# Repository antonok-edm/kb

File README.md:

# kb
This repository contains the full design files for my custom-designed keyboard.

Features:
- 68 keys
- compact ortholinear format
- carbon fiber construction
- full on-the-fly programmability
- HID Mouse functionality
- MIDI functionality
- Built-in Colemak layout
- 14-key HID rollover
- n-key MIDI rollover
- multiple function layers

## My setup
The keyboard's layouts are designed to be reprogrammed as needed. The user is free to assign keys to any HID-compliant controls or internal function calls at will. In this section, I describe the layouts that I use, included as a sample in this repository.

I currently have 7 different layers defined on my keyboard: Colemak, Qwerty, MIDI, Fn, Layer-Up, Layer-Down, and Mouse.

MIDI has a 4x12 grid of chromatic MIDI keys, providing 4 octaves of pitch-shiftable notes.

Fn has all standard function keys, as well as keyboard-internal functions like switching between layers.

Layer-Down puts symbols for programming, such as parenthesis and braces, on the home row so that they can be accessed more easily.

Layer-Up has a numpad.

Mouse puts cursor controls on the right side of the keyboard, with cursor speed controls operated by the left hand.

## Customizing the keyboard
The tool [kb-layout-manager](https://gitlab.com/antonok/kb-layout-manager) was created to make layout customization extremely easy and intuitive.
Manual customization is still possible by modifying the `layermaps.c` file.

`layermaps.c` includes the behavior of every key. Each key can take one of the following functions:

| Function | Description                                                                     | Examples                                                                 |
|----------|---------------------------------------------------------------------------------|--------------------------------------------------------------------------|
| HID      | Any standard keyboard key                                                       | <kbd>a</kbd>, <kbd>1</kbd>, <kbd>;</kbd>                                 |
| MOD      | At least one standard keyboard modifier                                         | <kbd>Left shift</kbd>, <kbd>Right control</kbd>                          |
| MIDI     | Any MIDI pitch                                                                  | C0 to G10                                                                |
| TOGGLE   | Switch to a different layer                                                     | Change to MIDI layer, switch to QWERTY layout                            |
| TARGET   | Switch to a different layer while the key is held (modifier-style)              | Access FN keys, use temporary layer shifts                               |
| FUNC     | Any arbitrary predefined function from the firmware                             | shift MIDI pitch, switch function layer                                  |
| CLICK    | Execute a click an HID mouse button                                             | left click, middle click, forward/back                                   |
| MOUSE    | Move the mouse cursor                                                           | horizontal or vertical                                                   |
| SCROLL   | Mouse scroll or pan                                                             | horizontal or vertical                                                   |
| HIDMOD   | Any standard keyboard key combined with at least one standard keyboard modifier | <kbd>ctrl</kbd>+<kbd>shift</kbd>+<kbd>m</kbd>, <kbd>{</kbd>, <kbd>?</kbd>|

Once modifications have been made to a layout, the firmware can be reflashed to the keyboard using the standard Teensy programmer over USB. The Teensy's bootloader
can be accessed without taking apart the keyboard by pressing a predefined key combination. The entire reflashing process takes about 3 seconds in total.

## Want to use this for your own keyboard?
If this project is useful at all for you, I'd love to hear about it!

The firmware is optimized for my own personal setup, but could be tweaked with minimal effort to suit different hardware. Please feel free to submit an issue, and I would
be happy to provide assistance with this.

### License information
Files from the LUFA library are released under the MIT license.
My custom design files are released under version 3 or later of the GPL.
License information for the LUFA library is available at www.lufa-lib.org.

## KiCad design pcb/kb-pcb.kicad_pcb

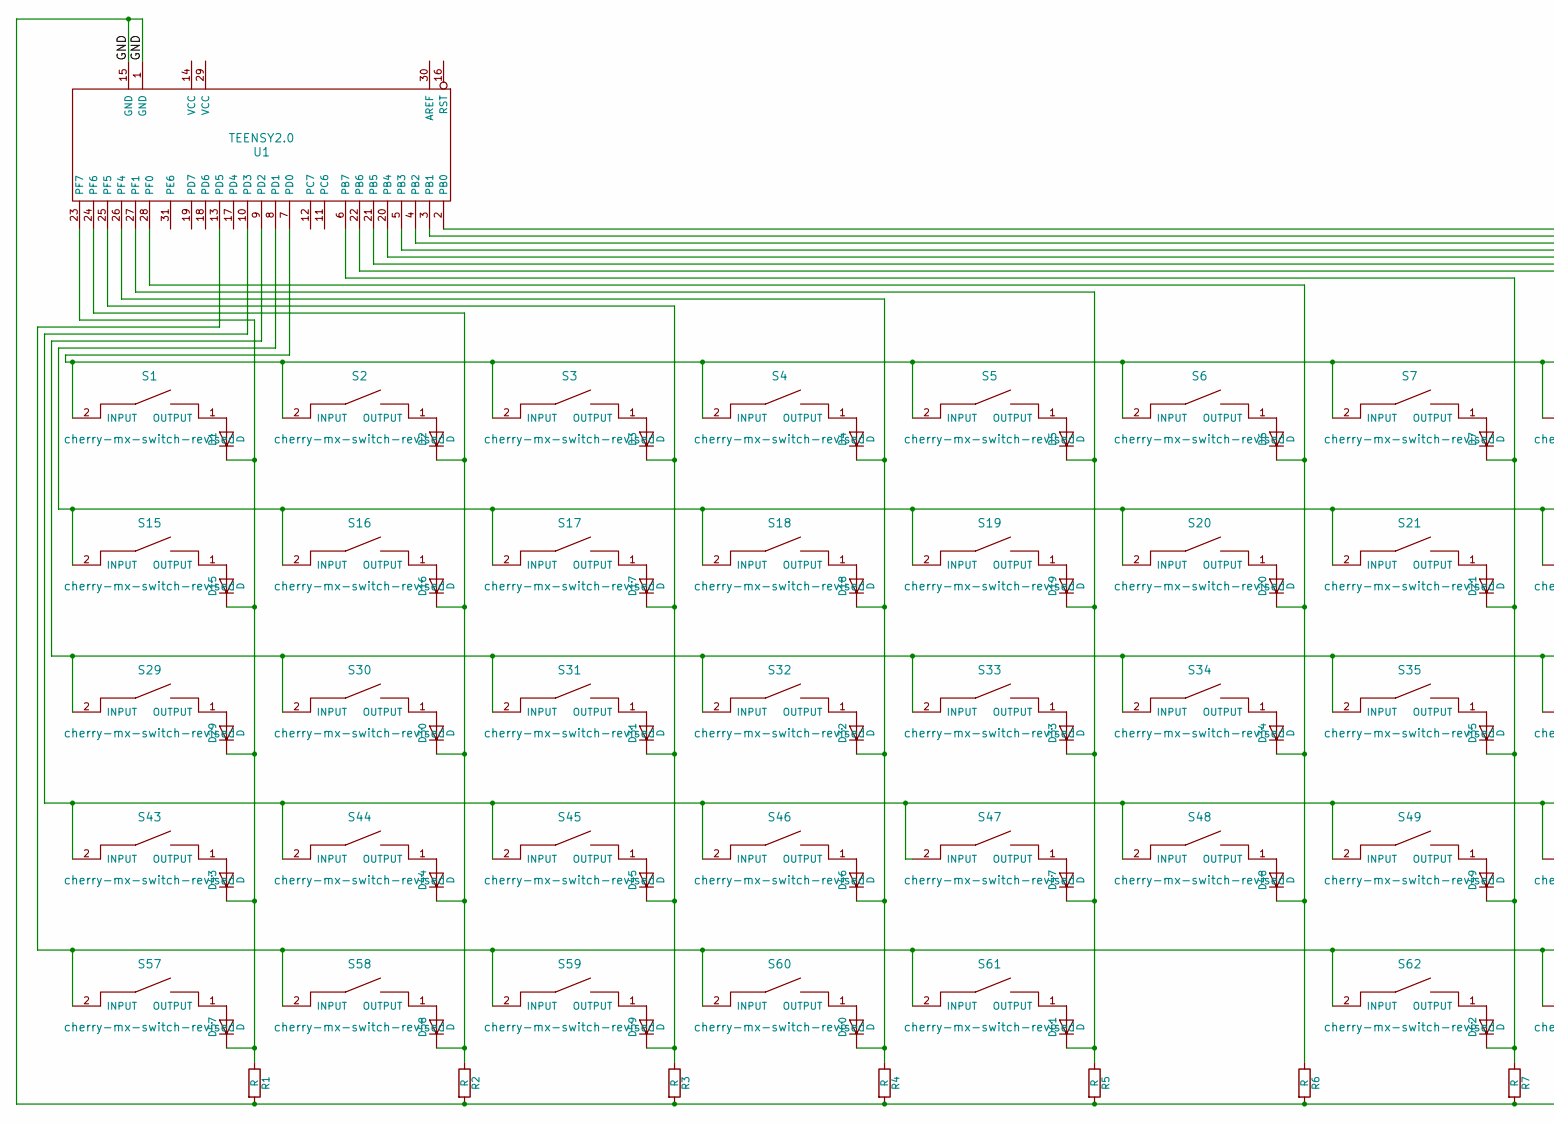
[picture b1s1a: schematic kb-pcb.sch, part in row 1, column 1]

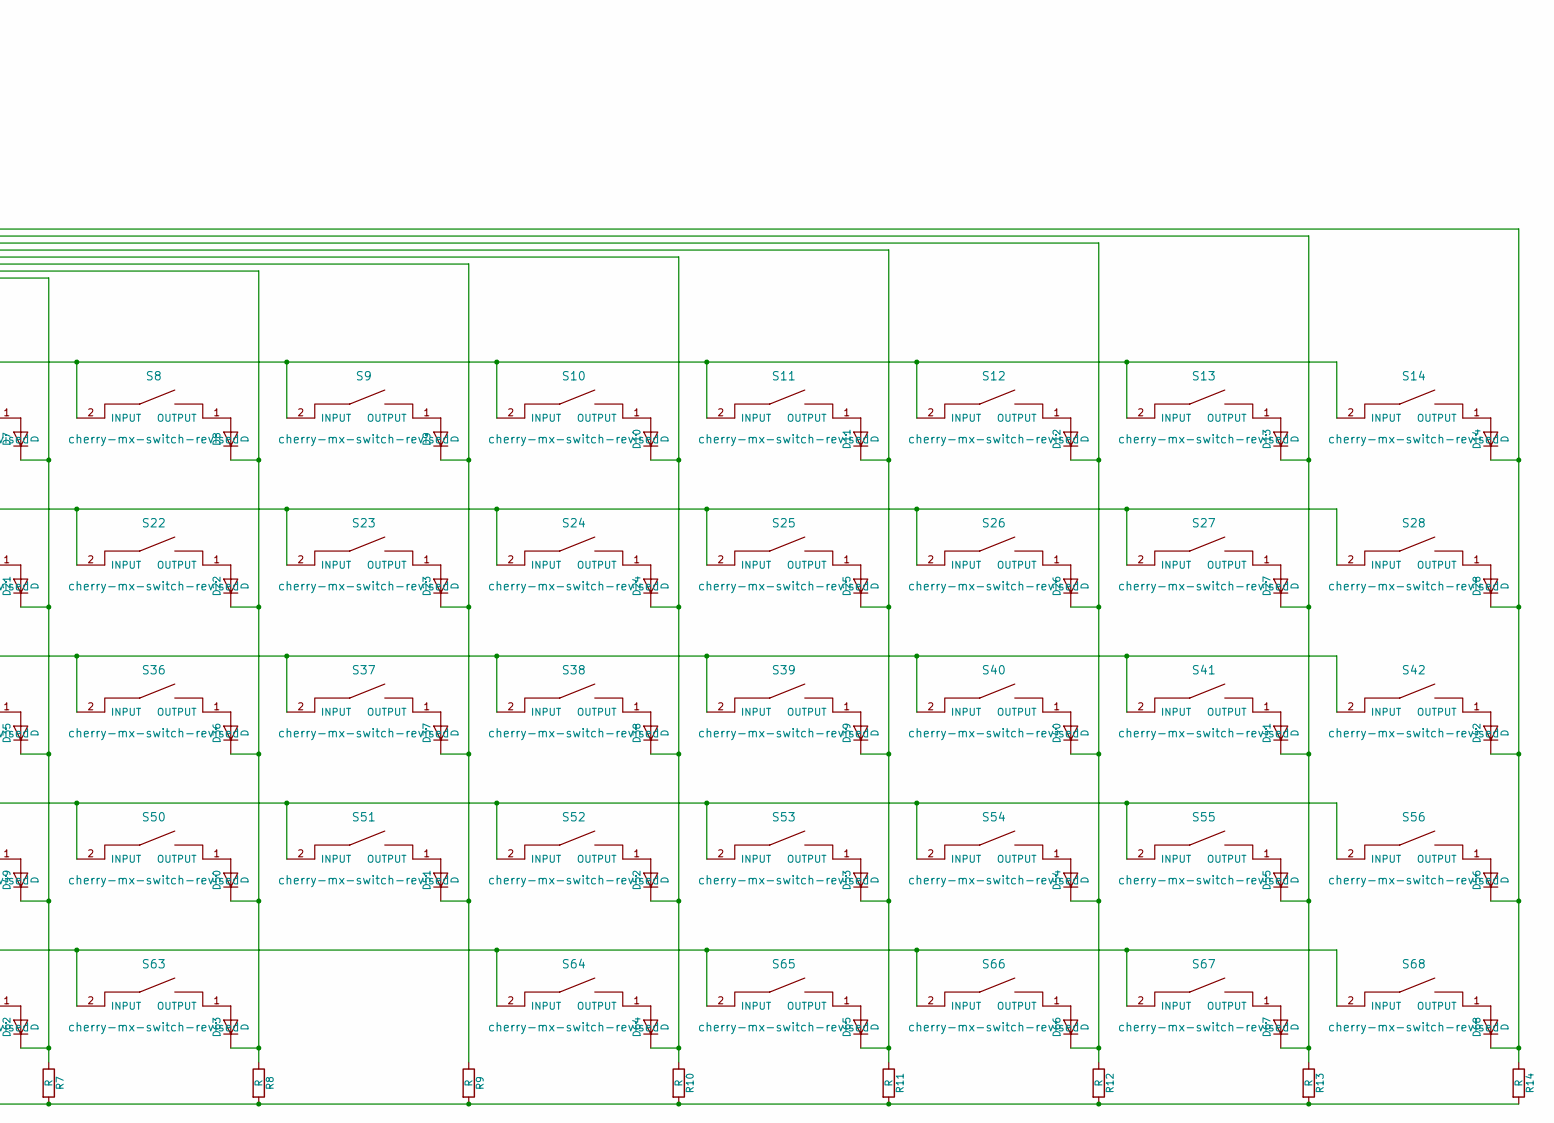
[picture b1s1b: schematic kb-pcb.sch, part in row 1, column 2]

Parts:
D1, D2, D3, D4, D5, D6, D7, D8, D9, D10, D11, D12, D13, D14, D15, D16, D17, D18, D19, D20, D21, D22, D23, D24, D25, D26, D27, D28, D29, D30, D31, D32, D33, D34, D35, D36, D37, D38, D39, D40, D41, D42, D43, D44, D45, D46, D47, D48, D49, D50, D51, D52, D53, D54, D55, D56, D57, D58, D59, D60, D61, D62, D63, D64, D65, D66, D67, D68: D; D_DO-35_SOD27_P7.62mm_Horizontal
R1, R2, R3, R4, R5, R6, R7, R8, R9, R10, R11, R12, R13, R14: R; Resistor_SMD+THTuniversal_0805to2512_RM10_HandSoldering
S1, S2, S3, S4, S5, S6, S7, S8, S9, S10, S11, S12, S13, S14, S15, S16, S17, S18, S19, S20, S21, S22, S23, S24, S25, S26, S27, S28, S29, S30, S31, S32, S33, S34, S35, S36, S37, S38, S39, S40, S41, S42, S43, S44, S45, S46, S47, S48, S49, S50, S51, S52, S53, S54, S55, S56, S57, S58, S59, S60, S65, S66, S67, S68: cherry-mx-switch-revised; key_1u
S61, S63: cherry-mx-switch-revised; key_1.75u
S62, S64: cherry-mx-switch-revised; key_1.25u
U1: TEENSY2.0; Teensy2.0

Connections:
/GND: R1.2, R2.2, R3.2, R4.2, R5.2, R6.2, R7.2, R8.2, R9.2, R10.2, R11.2, R12.2, R13.2, R14.2, U1.1 (GND), U1.15 (GND)
unnamed: D1.1 (K), D15.1 (K), D29.1 (K), D43.1 (K), D57.1 (K), R1.1, U1.23 (PF7)
unnamed: D1.2 (A), S1.1 (OUTPUT)
unnamed: D2.2 (A), S2.1 (OUTPUT)
unnamed: D3.2 (A), S3.1 (OUTPUT)
unnamed: D4.2 (A), S4.1 (OUTPUT)
unnamed: D5.2 (A), S5.1 (OUTPUT)
unnamed: D6.2 (A), S6.1 (OUTPUT)
unnamed: D7.2 (A), S7.1 (OUTPUT)
unnamed: D8.2 (A), S8.1 (OUTPUT)
unnamed: D9.2 (A), S9.1 (OUTPUT)
unnamed: D10.1 (K), D24.1 (K), D38.1 (K), D52.1 (K), D64.1 (K), R10.1, U1.20 (PB4)
unnamed: D10.2 (A), S10.1 (OUTPUT)
unnamed: D11.1 (K), D25.1 (K), D39.1 (K), D53.1 (K), D65.1 (K), R11.1, U1.5 (PB3)
unnamed: D11.2 (A), S11.1 (OUTPUT)
unnamed: D12.1 (K), D26.1 (K), D40.1 (K), D54.1 (K), D66.1 (K), R12.1, U1.4 (PB2)
unnamed: D12.2 (A), S12.1 (OUTPUT)
unnamed: D13.1 (K), D27.1 (K), D41.1 (K), D55.1 (K), D67.1 (K), R13.1, U1.3 (PB1)
unnamed: D13.2 (A), S13.1 (OUTPUT)
unnamed: D14.1 (K), D28.1 (K), D42.1 (K), D56.1 (K), D68.1 (K), R14.1, U1.2 (PB0)
unnamed: D14.2 (A), S14.1 (OUTPUT)
unnamed: D15.2 (A), S15.1 (OUTPUT)
unnamed: D2.1 (K), D16.1 (K), D30.1 (K), D44.1 (K), D58.1 (K), R2.1, U1.24 (PF6)
unnamed: D16.2 (A), S16.1 (OUTPUT)
unnamed: D3.1 (K), D17.1 (K), D31.1 (K), D45.1 (K), D59.1 (K), R3.1, U1.25 (PF5)
unnamed: D17.2 (A), S17.1 (OUTPUT)
unnamed: D4.1 (K), D18.1 (K), D32.1 (K), D46.1 (K), D60.1 (K), R4.1, U1.26 (PF4)
unnamed: D18.2 (A), S18.1 (OUTPUT)
unnamed: D5.1 (K), D19.1 (K), D33.1 (K), D47.1 (K), D61.1 (K), R5.1, U1.27 (PF1)
unnamed: D19.2 (A), S19.1 (OUTPUT)
unnamed: D6.1 (K), D20.1 (K), D34.1 (K), D48.1 (K), R6.1, U1.28 (PF0)
unnamed: D20.2 (A), S20.1 (OUTPUT)
unnamed: D7.1 (K), D21.1 (K), D35.1 (K), D49.1 (K), D62.1 (K), R7.1, U1.6 (PB7)
unnamed: D21.2 (A), S21.1 (OUTPUT)
unnamed: D8.1 (K), D22.1 (K), D36.1 (K), D50.1 (K), D63.1 (K), R8.1, U1.22 (PB6)
unnamed: D22.2 (A), S22.1 (OUTPUT)
unnamed: D9.1 (K), D23.1 (K), D37.1 (K), D51.1 (K), R9.1, U1.21 (PB5)
unnamed: D23.2 (A), S23.1 (OUTPUT)
unnamed: D24.2 (A), S24.1 (OUTPUT)
unnamed: D25.2 (A), S25.1 (OUTPUT)
unnamed: D26.2 (A), S26.1 (OUTPUT)
unnamed: D27.2 (A), S27.1 (OUTPUT)
unnamed: D28.2 (A), S28.1 (OUTPUT)
unnamed: D29.2 (A), S29.1 (OUTPUT)
unnamed: D30.2 (A), S30.1 (OUTPUT)
unnamed: D31.2 (A), S31.1 (OUTPUT)
unnamed: D32.2 (A), S32.1 (OUTPUT)
unnamed: D33.2 (A), S33.1 (OUTPUT)
unnamed: D34.2 (A), S34.1 (OUTPUT)
unnamed: D35.2 (A), S35.1 (OUTPUT)
unnamed: D36.2 (A), S36.1 (OUTPUT)
unnamed: D37.2 (A), S37.1 (OUTPUT)
unnamed: D38.2 (A), S38.1 (OUTPUT)
unnamed: D39.2 (A), S39.1 (OUTPUT)
unnamed: D40.2 (A), S40.1 (OUTPUT)
unnamed: D41.2 (A), S41.1 (OUTPUT)
unnamed: D42.2 (A), S42.1 (OUTPUT)
unnamed: D43.2 (A), S43.1 (OUTPUT)
unnamed: D44.2 (A), S44.1 (OUTPUT)
unnamed: D45.2 (A), S45.1 (OUTPUT)
unnamed: D46.2 (A), S46.1 (OUTPUT)
unnamed: D47.2 (A), S47.1 (OUTPUT)
unnamed: D48.2 (A), S48.1 (OUTPUT)
unnamed: D49.2 (A), S49.1 (OUTPUT)
unnamed: D50.2 (A), S50.1 (OUTPUT)
unnamed: D51.2 (A), S51.1 (OUTPUT)
unnamed: D52.2 (A), S52.1 (OUTPUT)
unnamed: D53.2 (A), S53.1 (OUTPUT)
unnamed: D54.2 (A), S54.1 (OUTPUT)
unnamed: D55.2 (A), S55.1 (OUTPUT)
unnamed: D56.2 (A), S56.1 (OUTPUT)
unnamed: D57.2 (A), S57.1 (OUTPUT)
unnamed: D58.2 (A), S58.1 (OUTPUT)
unnamed: D59.2 (A), S59.1 (OUTPUT)
unnamed: D60.2 (A), S60.1 (OUTPUT)
unnamed: D61.2 (A), S61.1 (OUTPUT)
unnamed: D62.2 (A), S62.1 (OUTPUT)
unnamed: D63.2 (A), S63.1 (OUTPUT)
unnamed: D64.2 (A), S64.1 (OUTPUT)
unnamed: D65.2 (A), S65.1 (OUTPUT)
unnamed: D66.2 (A), S66.1 (OUTPUT)
unnamed: D67.2 (A), S67.1 (OUTPUT)
unnamed: D68.2 (A), S68.1 (OUTPUT)
unnamed: S1.2 (INPUT), S2.2 (INPUT), S3.2 (INPUT), S4.2 (INPUT), S5.2 (INPUT), S6.2 (INPUT), S7.2 (INPUT), S8.2 (INPUT), S9.2 (INPUT), S10.2 (INPUT), S11.2 (INPUT), S12.2 (INPUT), S13.2 (INPUT), S14.2 (INPUT), U1.7 (PD0)
unnamed: S15.2 (INPUT), S16.2 (INPUT), S17.2 (INPUT), S18.2 (INPUT), S19.2 (INPUT), S20.2 (INPUT), S21.2 (INPUT), S22.2 (INPUT), S23.2 (INPUT), S24.2 (INPUT), S25.2 (INPUT), S26.2 (INPUT), S27.2 (INPUT), S28.2 (INPUT), U1.8 (PD1)
unnamed: S29.2 (INPUT), S30.2 (INPUT), S31.2 (INPUT), S32.2 (INPUT), S33.2 (INPUT), S34.2 (INPUT), S35.2 (INPUT), S36.2 (INPUT), S37.2 (INPUT), S38.2 (INPUT), S39.2 (INPUT), S40.2 (INPUT), S41.2 (INPUT), S42.2 (INPUT), U1.9 (PD2)
unnamed: S43.2 (INPUT), S44.2 (INPUT), S45.2 (INPUT), S46.2 (INPUT), S47.2 (INPUT), S48.2 (INPUT), S49.2 (INPUT), S50.2 (INPUT), S51.2 (INPUT), S52.2 (INPUT), S53.2 (INPUT), S54.2 (INPUT), S55.2 (INPUT), S56.2 (INPUT), U1.10 (PD3)
unnamed: S57.2 (INPUT), S58.2 (INPUT), S59.2 (INPUT), S60.2 (INPUT), S61.2 (INPUT), S62.2 (INPUT), S63.2 (INPUT), S64.2 (INPUT), S65.2 (INPUT), S66.2 (INPUT), S67.2 (INPUT), S68.2 (INPUT), U1.13 (PD5)

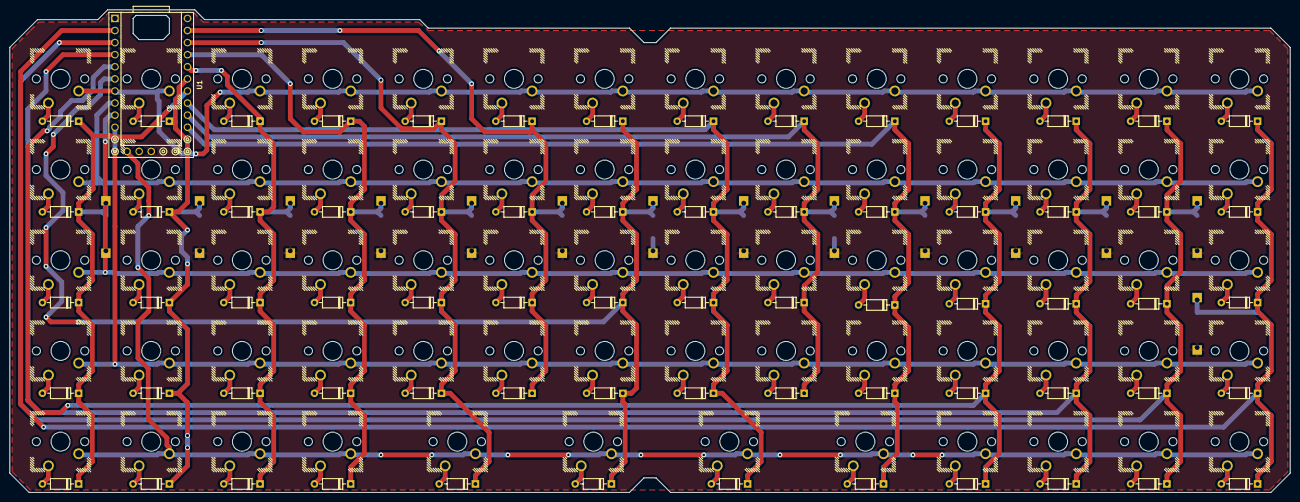
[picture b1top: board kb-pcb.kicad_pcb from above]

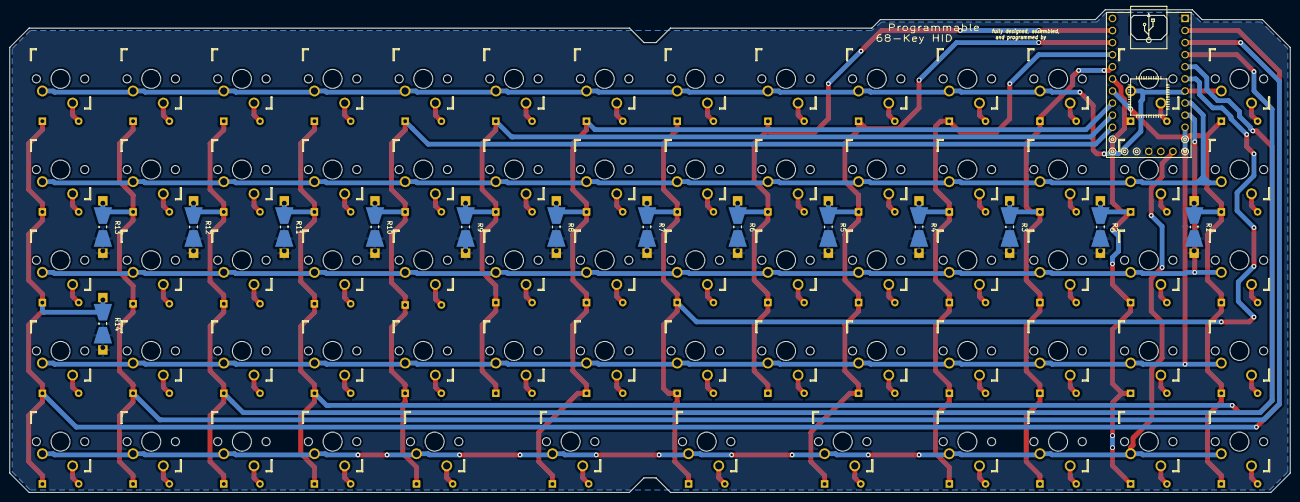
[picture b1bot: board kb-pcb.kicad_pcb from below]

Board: 2 copper layers, 269.0 x 101.4 mm, 151 parts (14 on the bottom side), 88 nets.

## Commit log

2017-10-27 add readme
2017-10-27 add license
2017-11-25 update layermap
2017-11-25 add space for center screw terminals to pcb
2017-11-25 add space on pcb above usb port for #4
2017-11-30 add solder points for pull-down resistors as in #3
2017-12-27 fix two unconnected resistors
2017-12-27 add OpenSCAD models
2017-12-27 add .gitignore files
2018-03-16 update layouts
2018-03-17 migrated layout customization to layermaps.c, minor enhancements
2018-03-18 update to account for kb-layout-manager
2018-03-29 Use saner default for midsection '$fn' value
2018-03-29 update layermaps
2018-09-14 move layermaps.c into separate submodule
2018-09-14 move all links to gitlab
2018-11-03 fixes strange behavior after layer toggles on some computers
2018-11-03 hot take: 8 spaces is too many spaces
2018-12-27 fix some stray indentation issues
2018-12-29 generalize layermaps to be indexed rather than named
2019-05-04 use standard kicad gitignore
2019-05-04 use XenGi/teensy.pretty as submodule
2019-05-04 upgrade to Kicad 5 footprints
    In doing so, I've updated the diodes to be N4148 diodes from the
    official modules. Since those have slightly different footprints from
    the original ones I used, I've modified the PCB layout accordingly.
    I lost track of the original Teensy 2.0 footprint I created, so I'm
    using a modified version of XenGi's footprint as well.
2019-05-04 improved silkscreening
    The details on the silkscreened microcontroller are really important.
    So is the little USB icon on the port.
